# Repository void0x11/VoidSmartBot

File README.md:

# 📦 VoidSmartBot Core V1.1

> A professionally engineered 4-layer PCB for mobile robotics and embedded systems.

---

## 🔧 Overview

**SmartBot Core V1.1** is a custom-designed control board tailored for mobile robotics platforms.  
Built on a 4-layer FR4 stack, it combines reliable power management, motor control, encoder support, and clean communication — all in a compact, Arduino Mega-compatible footprint.

---

## 🧠 Core Features

### 🔋 Power That Doesn’t Quit
- Dual battery input with seamless auto-switching (Power MUX)
- Over-voltage & over-current protection (TVS diode + SMD fuse)
- BAT1 / BAT2 source indicators via onboard LEDs

### ⚙️ Motion & I/O Control
- 4 DC motor outputs via integrated L298N (w/ flyback diodes)
- 4 quadrature encoder inputs (CHA/CHB)
- Support for ultrasonic sensors, servos, and I2C LCD modules

### 🛠️ Hardware Architecture
- ATmega2560 (Arduino Mega compatible)
- USB-B interface via CH340G (UART + programming)
- 54 digital I/O, 16 analog inputs, 14 PWM channels, 10-bit ADC
- 4-layer FR4 with internal GND & Power planes
- GND stitching vias for EMI noise reduction
- Clear silkscreen labeling & breakout headers
- Onboard diagnostic LEDs for 12V, 5V, MCU, and system power

---

## 📐 Board Dimensions

- 📏 Size: 130mm × 133mm  
- 🧩 Form Factor: Arduino Mega shield compatible

---

## 🖼️ Board Gallery

---

## 🧱 Schematic & PCB Layer Stack
Schematic

Layer 1 (Surface Mount)

Layer 2 (Light Signals, GND Refrence)

Layer 3 (Power Plane)

Layer 4 (Main Traces)

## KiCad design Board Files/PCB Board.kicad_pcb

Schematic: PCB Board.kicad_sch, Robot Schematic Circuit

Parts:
A1: A000067; MODULE_A000067; PARTREV 3
C1: 100nF; C_Disc_D8.0mm_W5.0mm_P5.00mm
D2: Red-LED; LED_1206_3216Metric
D3: 1N5819; D_DO-41_SOD81_P10.16mm_Horizontal
D4: Green-LED; LED_D3.0mm_Horizontal_O1.27mm_Z2.0mm
D5: BLUE-LED; LED_D3.0mm_Horizontal_O1.27mm_Z2.0mm
D6: Yellow-LED; LED_D3.0mm_Horizontal_O1.27mm_Z2.0mm
D7: Purple-LED; LED_D1.8mm_W1.8mm_H2.4mm_Horizontal_O3.81mm_Z1.6mm
D8: Orange-LED; LED_D1.8mm_W1.8mm_H2.4mm_Horizontal_O3.81mm_Z1.6mm
F1: 1812L110_24DR; FUSM4632X200N
H1, H2, H3, H4, H5, H6: MountingHole_Pad; MountingHole_3.2mm_M3_ISO7380_Pad
J1: Screw_Encoder_1; TerminalBlock_MaiXu_MX126-5.0-06P_1x06_P5.00mm
J2: Screw_Encoder_2; TerminalBlock_MaiXu_MX126-5.0-06P_1x06_P5.00mm
J3: Screw_Encoder_3; TerminalBlock_MaiXu_MX126-5.0-06P_1x06_P5.00mm
J4: Screw_Encoder_4; TerminalBlock_MaiXu_MX126-5.0-06P_1x06_P5.00mm
J5: Screw_HC-SR04; TerminalBlock_4Ucon_1x04_P3.50mm_Horizontal
J6: Screw_LCD; TerminalBlock_4Ucon_1x04_P3.50mm_Horizontal
J7: 12V DC-Jack; GCT_DCJ200-10-A-XX-K_REVA; PARTREV A
J8: Screw_Servos; TerminalBlock_MaiXu_MX126-5.0-06P_1x06_P5.00mm
J9: USB-B-S-X-X-TH; SAMTEC_USB-B-S-X-X-TH; PARTREV Q
J10: XT60-M; AMASS_XT60-M; PARTREV V1.2
Q1, Q2: IRF4905; TO-220-3_Vertical
R1A1: 200k; R_Axial_DIN0204_L3.6mm_D1.6mm_P5.08mm_Horizontal
R1C1: 230k; R_Axial_DIN0204_L3.6mm_D1.6mm_P5.08mm_Horizontal
R1D1: 24.9k; R_Axial_DIN0204_L3.6mm_D1.6mm_P5.08mm_Horizontal
R2, R3, R4, R5, R6, R7: 330; R_Axial_DIN0204_L3.6mm_D1.6mm_P5.08mm_Horizontal
S1: MINI-SPDT-SW; SW_MINI-SPDT-SW; PARTREV C
S2: RST; SW_BUTT-2; PARTREV N/A
U1, U2: L298N; TO127P2020X500X2100-15
U3: LV25-P; LEM_LV25-P
U4: HC-05; XCVR_HC-05; PARTREV v1.0
U5: LM7812_TO220; TO-220-3_Vertical
U6: LM7805_TO220; TO-220-3_Vertical
U7: TVS1800DRV; WSON-6-1EP_2x2mm_P0.65mm_EP1x1.6mm
U8: CH340C; SOIC-16_3.9x9.9mm_P1.27mm
U9: LTC4416IMS_PBF; MSOP-10_MS; MANUFACTURER_PART_NUMBER ltc4416ims1

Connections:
/+5V: J1.5, J2.5, J3.5, J4.5, J5.3, J6.3, J8.2, J8.5, R3.2, U1.9 (VSS), U2.9 (VSS), U6.3 (VO)
/+12V: R4.2, U1.4 (VS), U2.4 (VS), U5.3 (VO)
GND: A1.GND4, A1.GND5, D2.1 (K), D4.1 (K), D5.1 (K), D6.1 (K), H1.1, H2.1, H3.1, H4.1, H5.1, H6.1, J1.6, J2.6, J3.6, J4.6, J5.4, J6.4, J7.3, J8.3, J8.6, J9.4 (GND), J9.S1 (SHIELD), J9.S2 (SHIELD), J10.N (NEG), R1C1.1, S2.2, U1.8 (GND), U2.8 (GND), U3.3 (HV-), U3.6 (V-), U4.13 (GND), U4.21 (GND), U4.22 (GND), U5.2 (GND), U6.2 (GND), U7.1 (GND), U7.2 (GND), U7.3 (GND), U7.7 (GND), U8.1 (GND), U9.3 (GND), U9.4 (*E2)
unnamed: A1.3V3 (+3V3), U4.12 (3.3_VCC)
unnamed: A1.5V_2 (+5V_2), R5.2
unnamed: A1.RESET, C1.2, S2.1
unnamed: D2.2 (A), R2.1
unnamed: D3.2 (A), R2.2, S1.1, U5.1 (VI), U6.1 (VI)
unnamed: D3.1 (K), U3.1 (HV+)
unnamed: D4.2 (A), R3.1
unnamed: D5.2 (A), R4.1
unnamed: D6.2 (A), R5.1
unnamed: D7.2 (A), R6.1
unnamed: D7.1 (K), Q1.1 (G), U9.10 (G1)
unnamed: D8.2 (A), R7.1
unnamed: D8.1 (K), Q2.1 (G), U9.6 (G2)
unnamed: F1.2, S1.2, U7.4 (IN), U7.5 (IN), U7.6 (IN)
unnamed: J1.1, U1.2 (OUT1)
unnamed: J1.2, U1.3 (OUT2)
unnamed: A1.52, J1.3
unnamed: A1.50, J1.4
unnamed: J2.1, U1.13 (OUT3)
unnamed: J2.2, U1.14 (OUT4)
unnamed: A1.53, J2.3
unnamed: A1.51, J2.4
unnamed: J3.1, U2.2 (OUT1)
unnamed: J3.2, U2.3 (OUT2)
unnamed: A1.26, J3.3
unnamed: A1.24, J3.4
unnamed: J4.1, U2.13 (OUT3)
unnamed: J4.2, U2.14 (OUT4)
unnamed: A1.25, J4.3
unnamed: A1.27, J4.4
unnamed: A1.5, J5.1
unnamed: A1.4, J5.2
unnamed: A1.20, J6.1
unnamed: A1.21, J6.2
unnamed: A1.45, J8.1
unnamed: A1.43, J8.4
unnamed: J9.3 (D+), U8.5 (UD+)
unnamed: J9.2 (D-), U8.6 (UD-)
unnamed: J9.1 (VCC), U8.16 (VCC)
unnamed: J10.P (POS), Q2.2 (D), U9.7 (V2)
unnamed: J7.1, Q1.2 (D), R1A1.2, U9.9 (V1)
unnamed: F1.1, Q1.3 (S), Q2.3 (S), R6.2, R7.2, U9.8 (VS)
unnamed: A1.39, U1.6 (ENA)
unnamed: A1.41, U1.11 (ENB)
unnamed: A1.42, U1.5 (IN1)
unnamed: A1.44, U1.7 (IN2)
unnamed: A1.46, U1.10 (IN3)
unnamed: A1.48, U1.12 (IN4)
unnamed: A1.38, U2.6 (ENA)
unnamed: A1.40, U2.11 (ENB)
unnamed: A1.34, U2.5 (IN1)
unnamed: A1.32, U2.7 (IN2)
unnamed: A1.30, U2.10 (IN3)
unnamed: A1.28, U2.12 (IN4)
unnamed: A1.AD0, U3.4 (M)
unnamed: A1.VIN, U3.5 (V+)
unnamed: A1.12, U4.2 (UART-RX)
unnamed: A1.13, U4.1 (UART-TX)
unnamed: A1.18, U8.3 (RXD)
unnamed: A1.19, U8.2 (TXD)
unnamed: C1.1, U8.13 (~DTR)
unnamed: R1A1.1, R1C1.2, R1D1.2, U9.2 (E1)
unnamed: R1D1.1, U9.1 (H1)

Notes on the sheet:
SCL
+5V
5V Power Rail Indicator
GND
BATT 2 Backup Battery
OUT 4
BAT1 Active (Main)
CHB
F.Cu Layer GND Shield
Power Protection Module
ECHO
USB-B UART Interface
OUT 1
Motor 3
Switch Power Rail Indicator
OUT 2
Power MUX Module
CHA
OUT 3
12V Power Rail Indicator
BAT2 Active (Backup)
TILT_SERVO
SDA
V_FAIL = 11V V_RESTORE = 12.2V
TVS Voltage Protection
Arduino Indicator
1.1A Fuse Protection
Motor 1
BATT 1 MAIN Battery
Motor 2
Motor 4
TRIG
BASE_SERVO

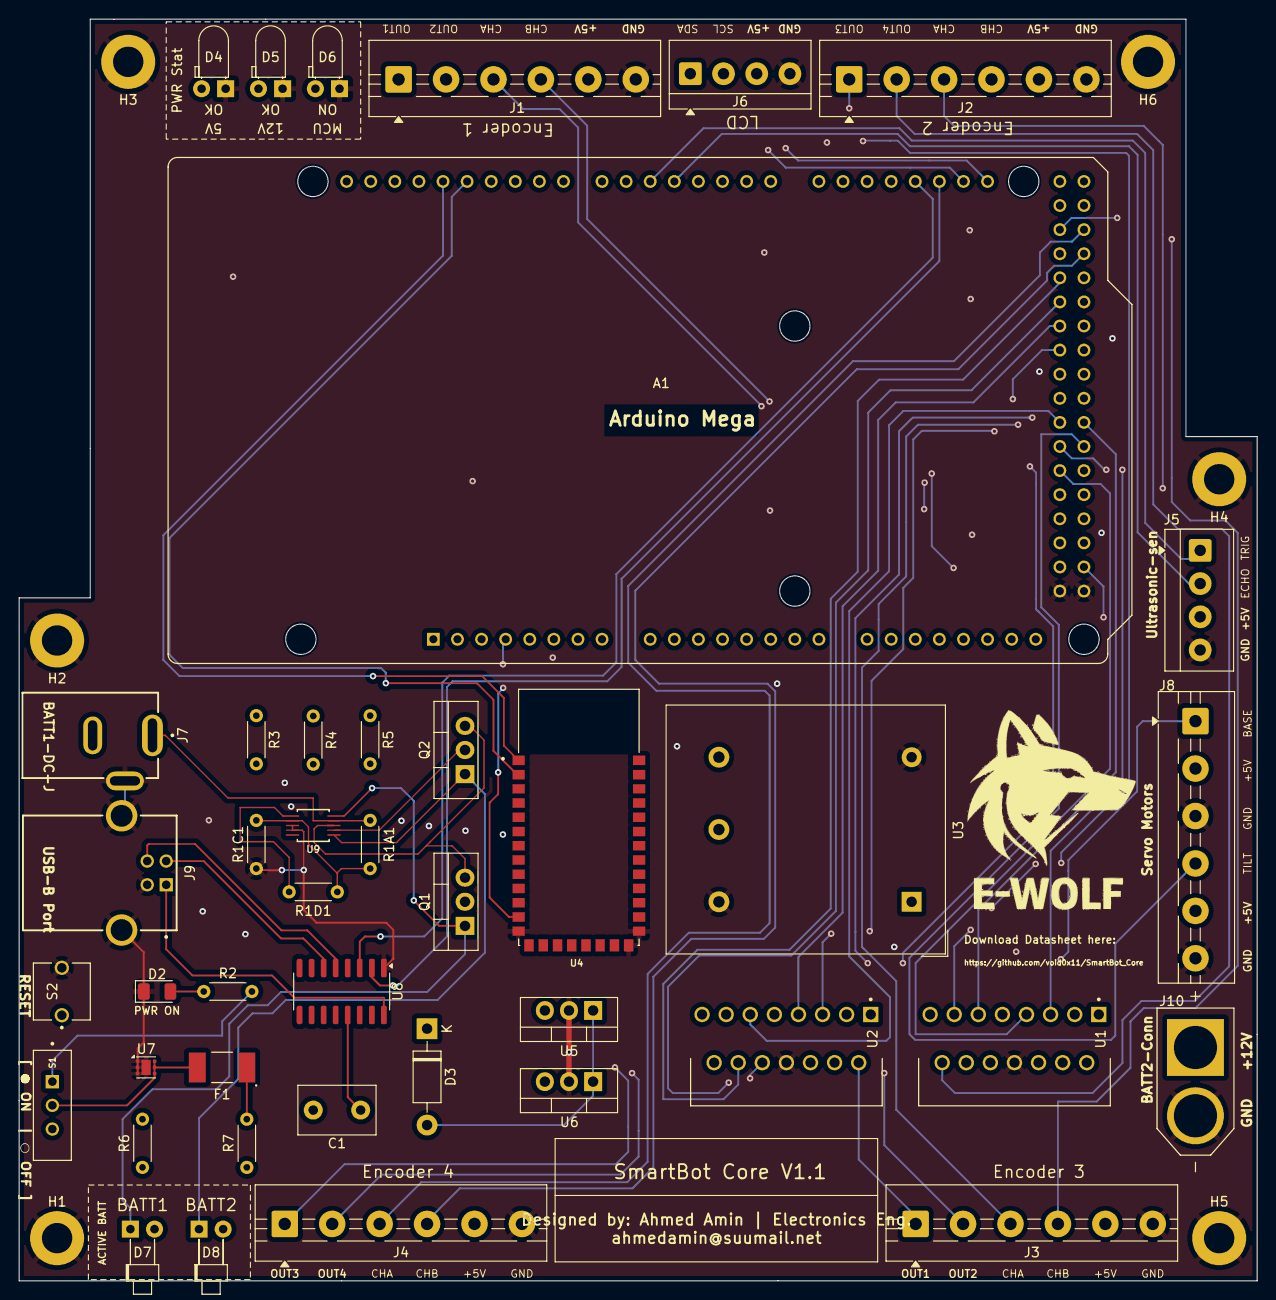
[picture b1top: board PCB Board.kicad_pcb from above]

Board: 4 copper layers, 130.5 x 133.0 mm, 48 parts (0 on the bottom side), 66 nets.

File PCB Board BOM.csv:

Reference,Value,Footprint,Datasheet,Qty,DNP,Exclude from BOM,Exclude from Board
A1,A000067,MyParts:MODULE_A000067,,1,,,
C1,100nF,Capacitor_THT:C_Disc_D8.0mm_W5.0mm_P5.00mm,~,1,,,
D2,Red-LED,LED_SMD:LED_1206_3216Metric,~,1,,,
D3,1N5819,Diode_THT:D_DO-41_SOD81_P10.16mm_Horizontal,http://www.vishay.com/docs/88525/1n5817.pdf,1,,,
D4,Green-LED,LED_THT:LED_D3.0mm_Horizontal_O1.27mm_Z2.0mm,~,1,,,
D5,BLUE-LED,LED_THT:LED_D3.0mm_Horizontal_O1.27mm_Z2.0mm,~,1,,,
D6,Yellow-LED,LED_THT:LED_D3.0mm_Horizontal_O1.27mm_Z2.0mm,~,1,,,
D7,Purple-LED,LED_THT:LED_D1.8mm_W1.8mm_H2.4mm_Horizontal_O3.81mm_Z1.6mm,~,1,,,
D8,Orange-LED,LED_THT:LED_D1.8mm_W1.8mm_H2.4mm_Horizontal_O3.81mm_Z1.6mm,~,1,,,
F1,1812L110_24DR,MyParts:FUSM4632X200N,,1,,,
"H1,H2,H3,H4,H5,H6",MountingHole_Pad,MountingHole:MountingHole_3.2mm_M3_ISO7380_Pad,~,6,,Excluded from BOM,
J1,Screw_Encoder_1,TerminalBlock:TerminalBlock_MaiXu_MX126-5.0-06P_1x06_P5.00mm,~,1,,,
J2,Screw_Encoder_2,TerminalBlock:TerminalBlock_MaiXu_MX126-5.0-06P_1x06_P5.00mm,~,1,,,
J3,Screw_Encoder_3,TerminalBlock:TerminalBlock_MaiXu_MX126-5.0-06P_1x06_P5.00mm,~,1,,,
J4,Screw_Encoder_4,TerminalBlock:TerminalBlock_MaiXu_MX126-5.0-06P_1x06_P5.00mm,~,1,,,
J5,Screw_HC-SR04,TerminalBlock_4Ucon:TerminalBlock_4Ucon_1x04_P3.50mm_Horizontal,~,1,,,
J6,Screw_LCD,TerminalBlock_4Ucon:TerminalBlock_4Ucon_1x04_P3.50mm_Horizontal,~,1,,,
J7,12V DC-Jack,MyParts:GCT_DCJ200-10-A-XX-K_REVA,,1,,,
J8,Screw_Servos,TerminalBlock:TerminalBlock_MaiXu_MX126-5.0-06P_1x06_P5.00mm,~,1,,,
J9,USB-B-S-X-X-TH,MyParts:SAMTEC_USB-B-S-X-X-TH,,1,,,
J10,XT60-M,MyParts:AMASS_XT60-M,,1,,,
"Q1,Q2",IRF4905,Package_TO_SOT_THT:TO-220-3_Vertical,http://www.infineon.com/dgdl/irf4905.pdf?fileId=5546d4625336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,2,,,
R1A1,200k,Resistor_THT:R_Axial_DIN0204_L3.6mm_D1.6mm_P5.08mm_Horizontal,~,1,,,
R1C1,230k,Resistor_THT:R_Axial_DIN0204_L3.6mm_D1.6mm_P5.08mm_Horizontal,~,1,,,
R1D1,24.9k,Resistor_THT:R_Axial_DIN0204_L3.6mm_D1.6mm_P5.08mm_Horizontal,~,1,,,
"R2,R3,R4,R5,R6,R7",330,Resistor_THT:R_Axial_DIN0204_L3.6mm_D1.6mm_P5.08mm_Horizontal,~,6,,,
S1,MINI-SPDT-SW,MyParts:SW_MINI-SPDT-SW,,1,,,
S2,RST,MyParts:SW_BUTT-2,,1,,,
"U1,U2",L298N,MyParts:TO127P2020X500X2100-15,,2,,,
U3,LV25-P,Sensor_Voltage:LEM_LV25-P,https://www.lem.com/sites/default/files/products_datasheets/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,1,,,
U4,HC-05,MyParts:XCVR_HC-05,,1,,,
U5,LM7812_TO220,Package_TO_SOT_THT:TO-220-3_Vertical,https://www.onsemi.cn/PowerSolutions/document/MC7800-D.PDF,1,,,
U6,LM7805_TO220,Package_TO_SOT_THT:TO-220-3_Vertical,https://www.onsemi.cn/PowerSolutions/document/MC7800-D.PDF,1,,,
U7,TVS1800DRV,Package_SON:WSON-6-1EP_2x2mm_P0.65mm_EP1x1.6mm,http://www.ti.com/lit/ds/symlink/tvs1800.pdf,1,,,
U8,CH340C,Package_SO:SOIC-16_3.9x9.9mm_P1.27mm,https://datasheet.lcsc.com/szlcsc/Jiangsu-Qin-Heng-CH340C_C8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,1,,,
U9,LTC4416IMS_PBF,MyParts:MSOP-10_MS,,1,,,

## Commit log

2025-05-29 v1.1
